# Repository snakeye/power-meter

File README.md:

# Power Meter

Power Meter is a microcontroller-based current consumption meter.
It samples current with an external ADC, computes rolling values in firmware, and displays live readings on a small OLED screen.

This repository is organized around two parts:
- `firmware/` - PlatformIO project with STM32 firmware
- `hardware/` - KiCad schematic/PCB and symbol/footprint libraries

## Project status

This is an early public version. Core measurement and display flow is implemented, while some features are still work in progress.

Implemented:
- ADC continuous sampling using ADS1220 DRDY interrupt
- Raw-to-current conversion (microamps)
- On-screen display of averaged current, elapsed time, and accumulated charge estimate
- Reset of measurement session from button A

Not implemented yet / needs refinement:
- Persistent configuration load/save (`loadConfig`, `saveConfig` are currently stubs)
- Button B action (handler is empty)
- Charge accumulation algorithm validation and unit correctness improvements

## Quick start

Prerequisites:
- PlatformIO CLI installed
- ST-Link connected to target board

Build firmware:

```bash
cd firmware
platformio run
```

Flash firmware:

```bash
cd firmware
platformio run -t upload
```

Current default PlatformIO environment targets STM32G431C8 (`STM32G431C8T6`).

## Documentation

Use these documents as the main reference:
- `docs/overview.md` - project overview and data flow
- `docs/architecture.md` - system architecture and runtime model
- `docs/firmware.md` - firmware modules and behavior
- `docs/hardware.md` - hardware components and repository artifacts
- `docs/build-and-flash.md` - setup, build, flash, and debug workflow
- `docs/roadmap.md` - known issues and next milestones

## Notes for contributors

- Prefer documenting real current behavior over intended behavior.
- Keep units explicit (`uA`, `mA`, `mAh`, `us`, `ms`) in code and docs.
- If you change measurement math, update `docs/firmware.md` accordingly.

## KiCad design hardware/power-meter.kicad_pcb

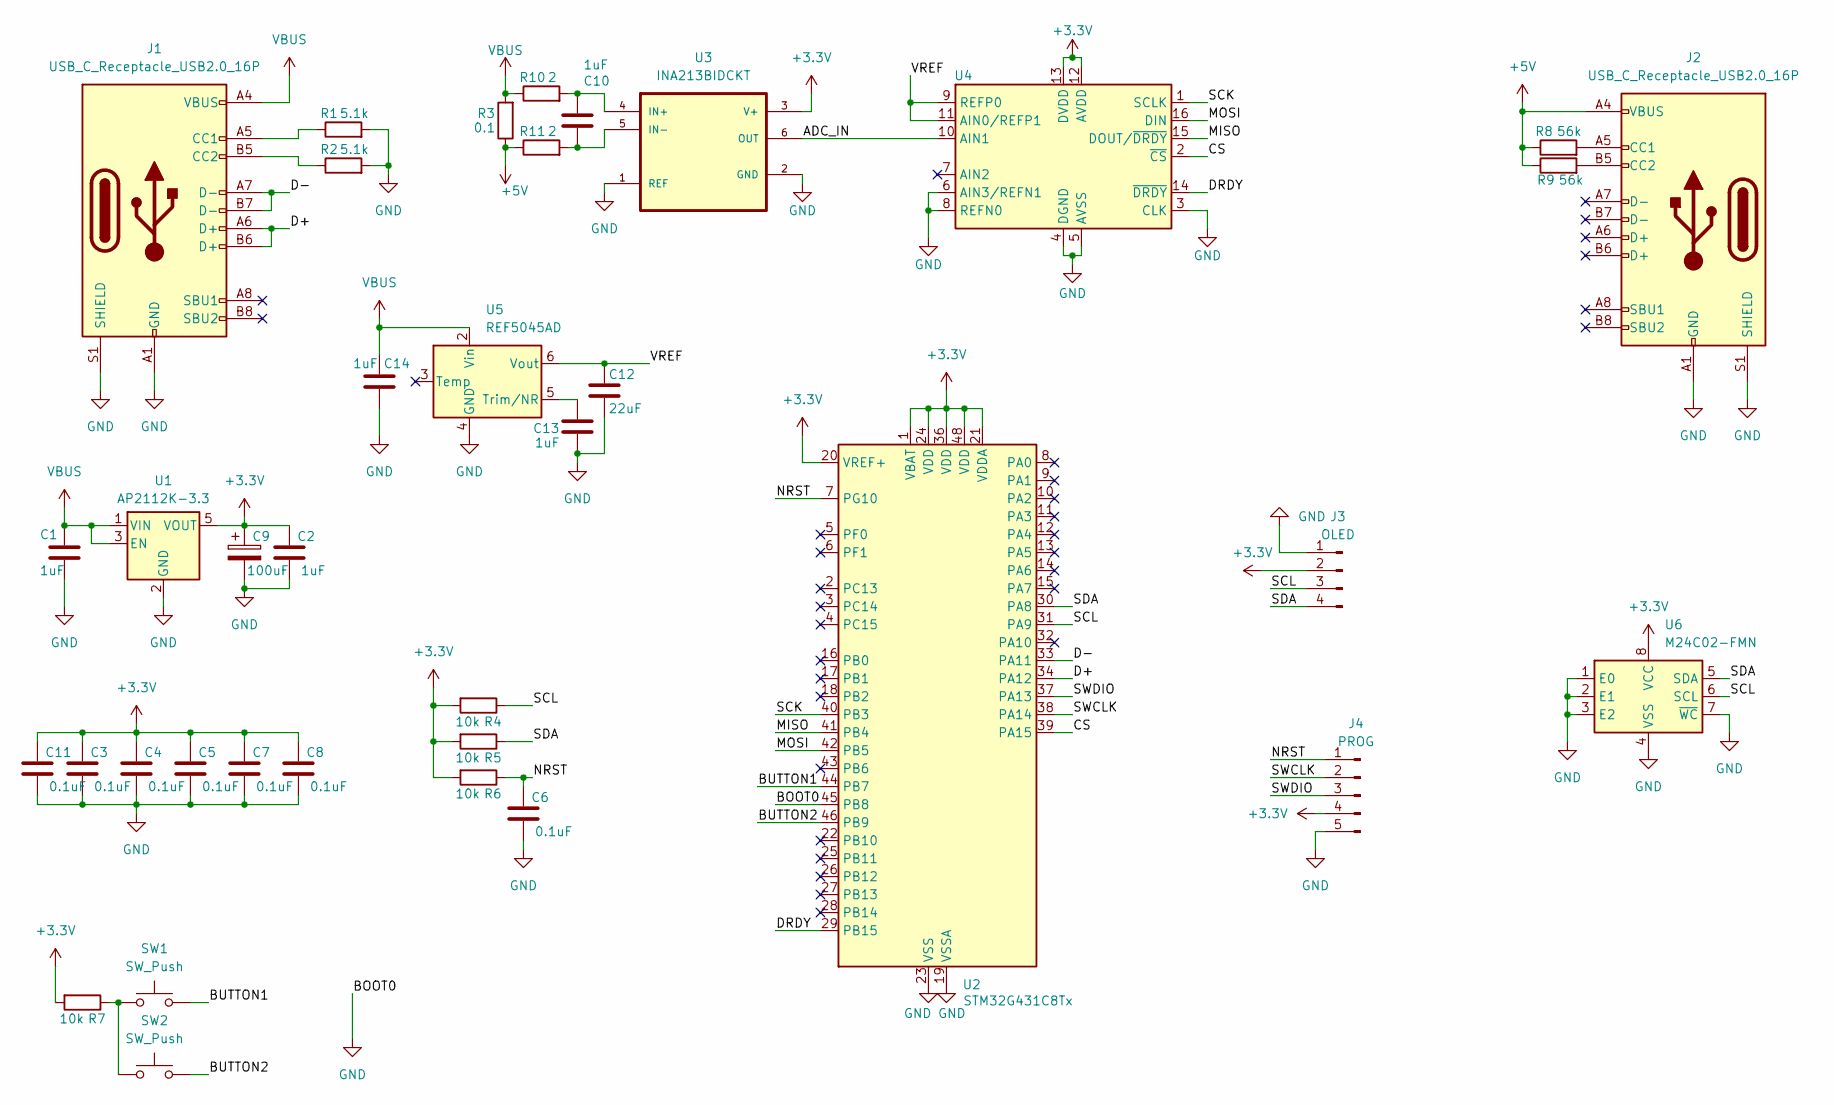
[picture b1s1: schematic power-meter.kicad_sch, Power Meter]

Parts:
C1, C2, C10, C13, C14: 1uF; C_0603_1608Metric
C3, C4, C5, C6, C7, C8, C11: 0.1uF; C_0603_1608Metric
C9: 100uF; CP_EIA-3216-18_Kemet-A
C12: 22uF; C_0603_1608Metric
J1, J2: USB_C_Receptacle_USB2.0_16P; USB_C_Receptacle_Palconn_UTC16-G
J3: OLED; Display_128x64_096_I2C
J4: PROG; PinSocket_1x05_P2.54mm_Vertical_SMD_Pin1Right
R1, R2: 5.1k; R_0603_1608Metric
R3: 0.1; R_2512_6332Metric
R4, R5, R6, R7: 10k; R_0603_1608Metric
R8, R9: 56k; R_0603_1608Metric
R10, R11: 2; R_0603_1608Metric
SW1, SW2: SW_Push; BUTTON
U1: AP2112K-3.3; SOT-23-5
U2: STM32G431C8Tx; LQFP-48_7x7mm_P0.5mm
U3: INA213BIDCKT; SOT-363_SC-70-6
U4: ADS1220xPW; TSSOP-16_4.4x5mm_P0.65mm
U5: REF5045AD; SOIC-8_3.9x4.9mm_P1.27mm
U6: M24C02-FMN; SOIC-8_3.9x4.9mm_P1.27mm

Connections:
+3.3V: C2.1, C3.1, C4.1, C5.1, C7.1, C8.1, C9.1, C11.1, J3.2, J4.4, R4.2, R5.2, R6.2, R7.2, U1.5 (VOUT), U2.1 (VBAT), U2.20 (VREF+), U2.21 (VDDA), U2.24 (VDD), U2.36 (VDD), U2.48 (VDD), U3.3 (V+), U4.12 (AVDD), U4.13 (DVDD), U6.8 (VCC)
+5V: J2.A4 (VBUS), J2.A9 (VBUS), J2.B4 (VBUS), J2.B9 (VBUS), R3.1, R8.1, R9.1, R11.1
/ADC_IN: U3.6 (OUT), U4.10 (AIN1)
/BUTTON1: SW1.2, U2.44 (PB7)
/BUTTON2: SW2.2, U2.46 (PB9)
/CS: U2.39 (PA15), U4.2 (~CS)
/D+: J1.A6 (D+), J1.B6 (D+), U2.34 (PA12)
/D-: J1.A7 (D-), J1.B7 (D-), U2.33 (PA11)
/DRDY: U2.29 (PB15), U4.14 (~DRDY)
/MISO: U2.41 (PB4), U4.15 (DOUT/~DRDY)
/MOSI: U2.42 (PB5), U4.16 (DIN)
/NRST: C6.1, J4.1, R6.1, U2.7 (PG10)
/SCK: U2.40 (PB3), U4.1 (SCLK)
/SCL: J3.3, R4.1, U2.31 (PA9), U6.6 (SCL)
/SDA: J3.4, R5.1, U2.30 (PA8), U6.5 (SDA)
/SWCLK: J4.2, U2.38 (PA14)
/SWDIO: J4.3, U2.37 (PA13)
/VREF: C12.1, U4.9 (REFP0), U4.11 (AIN0/REFP1), U5.6 (Vout)
GND: C1.2, C2.2, C3.2, C4.2, C5.2, C6.2, C7.2, C8.2, C9.2, C11.2, C12.2, C13.2, C14.2, J1.A1 (GND), J1.A12 (GND), J1.B1 (GND), J1.B12 (GND), J1.S1 (SHIELD), J2.A1 (GND), J2.A12 (GND), J2.B1 (GND), J2.B12 (GND), J2.S1 (SHIELD), J3.1, J4.5, R1.2, R2.2, U1.2 (GND), U2.19 (VSSA), U2.23 (VSS), U2.35 (VSS), U2.45 (PB8), U2.47 (VSS), U3.1 (REF), U3.2 (GND), U4.3 (CLK), U4.4 (DGND), U4.5 (AVSS), U4.6 (AIN3/REFN1), U4.8 (REFN0), U5.4 (GND), U6.1 (E0), U6.2 (E1), U6.3 (E2), U6.4 (VSS), U6.7 (~WC)
unnamed: J1.A5 (CC1), R1.1
unnamed: J1.B5 (CC2), R2.1
unnamed: J2.A5 (CC1), R8.2
unnamed: J2.B5 (CC2), R9.2
unnamed: R7.1, SW1.1, SW2.1
unnamed: C10.1, R10.2, U3.4 (IN+)
unnamed: C10.2, R11.2, U3.5 (IN-)
unnamed: C13.1, U5.5 (Trim/NR)
VBUS: C1.1, C14.1, J1.A4 (VBUS), J1.A9 (VBUS), J1.B4 (VBUS), J1.B9 (VBUS), R3.2, R10.1, U1.1 (VIN), U1.3 (EN), U5.2 (Vin)

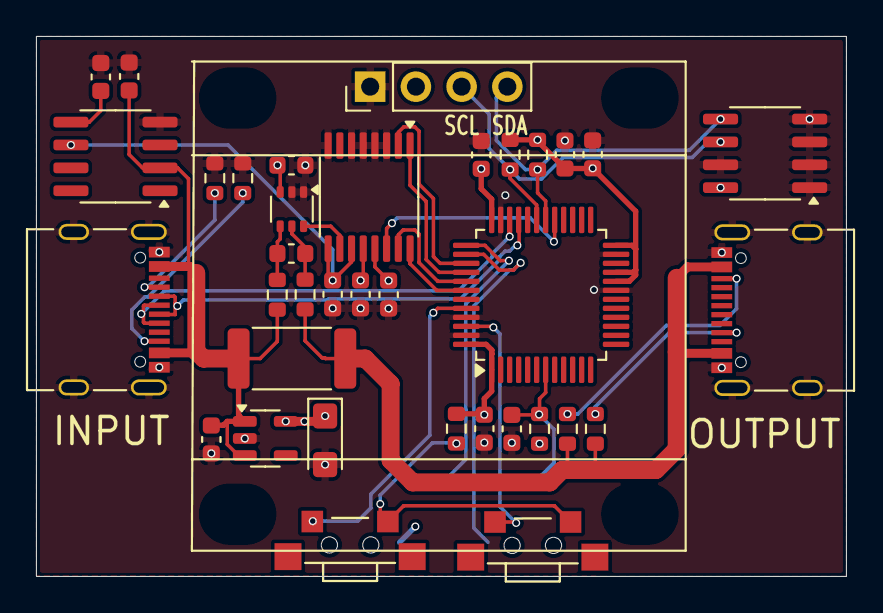
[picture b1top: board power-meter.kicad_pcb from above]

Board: 4 copper layers, 45.0 x 30.0 mm, 37 parts (1 on the bottom side), 28 nets.

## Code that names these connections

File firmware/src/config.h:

#pragma once

#include <Arduino.h>

#define PIN_I2C_SDA PA8
#define PIN_I2C_SCL PA9

#define PIN_CS PA15
#define PIN_SCK PB3
#define PIN_MISO PB4
#define PIN_MOSI PB5
#define PIN_DRDY PB15

#define PIN_BTN_A PB7
#define PIN_BTN_B PB9

// Constants
constexpr int32_t shuntResistance = 100; // Shunt resistance, milliOhms
constexpr int32_t ina213gain = 50;       // Gain INA213

constexpr int32_t adcResolution = 1 << 23; // 2^23 for the 24-bit ADC, 8388608 counts.

//
struct Config
{
    int32_t referenceVoltage; // milliVolts
    int32_t adcZeroOffset;
    int32_t adcGain;
    uint8_t adcRateMode;
};

extern Config config;

bool loadConfig();
void saveConfig();

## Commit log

2025-01-01 PCB v1
2025-01-01 OLED power fixed
2025-01-25 Platformio project; Display library
2025-01-25 Add renovate.json
2026-05-14 feat: v2
    Consolidate all work related to hardware revision v2 and firmware migration for that revision.
    Hardware scope:
    - Redesign PCB/schematic from v1 to v2 with updated component and connectivity decisions.
    - Add STM32G431 symbol/library assets used by the new design.
    - Integrate board-level corrections performed after first v2 routing pass.
    Firmware scope:
2026-05-14 feat: v1
    Consolidate all work related to hardware revision v1 and its initial firmware.
    Hardware scope:
    - Add the first complete KiCad project for power-meter board revision v1.
    - Introduce custom symbols/footprints and library table configuration required for the design.
    - Capture iterative PCB/schematic adjustments made during board bring-up.
    - Apply power-path fix for OLED supply and related project updates.
2026-05-14 docs: add architecture and documentation hub
    Add a structured documentation set for project overview, firmware, hardware, architecture, build/flash workflow, and roadmap.
    Changes:
    - Expand README navigation into a docs entry point.
    - Add architecture and subsystem documentation.
    - Add build-and-flash instructions and project overview pages.
    - Document hardware/firmware boundaries and development direction.
2026-05-14 fix: correct charge integration and mAh conversion
    Use physically correct I*dt accumulation, fix uA*us to mAh scaling, and add hardware math plus known-issues documentation to support calibration and validation.
2026-05-14 feat: add M24C02 config persistence and improve capacity display
    Persist runtime config to external I2C EEPROM with CRC validation and page writes, and show charge as one-decimal mAh for better low-current visibility.
2026-05-14 feat: add raw ADC zero calibration on button hold
    Calibrate zero offset from stable raw ADS1220 samples on 2s button B hold, persist it to EEPROM, and show short status messages for reset/calibration actions.
2026-05-14 fix: guard shared ADC state with critical sections
2026-05-14 fix: remove non-reentrant 64-bit micros tracking
2026-05-14 refactor: move ADC SPI read out of ISR
2026-05-14 refactor: use int32 for measurement buffer values
2026-05-14 fix: harden ADC data path against races and move SPI work out of ISR (#2)
    * fix: correct charge integration and mAh conversion
    Use physically correct I*dt accumulation, fix uA*us to mAh scaling, and add hardware math plus known-issues documentation to support calibration and validation.
    * feat: add M24C02 config persistence and improve capacity display
    Persist runtime config to external I2C EEPROM with CRC validation and page writes, and show charge as one-decimal mAh for better low-current visibility.
    * feat: add raw ADC zero calibration on button hold
    Calibrate zero offset from stable raw ADS1220 samples on 2s button B hold, persist it to EEPROM, and show short status messages for res
2026-05-14 feat: add ADC settings menu and calibration diagnostics
2026-05-16 docs: Added device picture
2026-05-16 license: added license file
